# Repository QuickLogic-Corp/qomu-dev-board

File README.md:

# qomu-dev-board
Qomu Development Board for EOS S3

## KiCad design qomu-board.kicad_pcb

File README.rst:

======================
Qomu Development Board
======================

.. figure:: img/qomu-board.png

Overview
========

This repository contains open hardware design files for a development board based on the Quicklogic `EOS S3 Sensor Processing Platform <https://www.quicklogic.com/products/eos-s3/>`_.
The design files were created by `Antmicro <https://www.antmicro.com>`_ in cooperation with `Quicklogic <https://www.quicklogic.com/>`_.
The board is small enough to fit into a USB socket.
This allows the user to explore functionalities of the EOS S3 platform on the go without cables or taking up space on your desk.
The board has an additional break-away part with debug connectors that speed up initial bringup and software development.

Key features
============

* EOS S3 Sensor Processing Platform
* 16Mbit of external flash memory
* Accelerometer
* User RGB LED
* Capacitive touch pads
* Supplied with 5.0VDC from USB port
* USB data signals tied to programmable logic

Layout and dimensions
=====================

.. figure:: img/qomu-layout.png

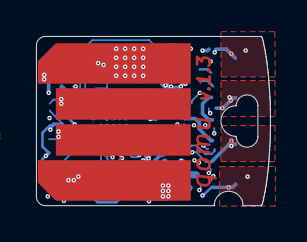
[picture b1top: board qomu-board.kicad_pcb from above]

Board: 4 copper layers, 13.0 x 9.4 mm, 52 parts (0 on the bottom side), 36 nets.

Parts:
C1, C2, C7, C9: 2u2, 10V, X5R, 0201; C_0201_0603Metric
C3, C5, C6, C8, C10, C11: 100n, 6.3V, X5R, 0201; C_0201_0603Metric
C4: 1u, 6.3V, X5R, 0201; C_0201
C13, C14: 8p, 25V, NP0, 0201; C_0201_0603Metric
C15: 1u, 6.3V, X5R, 0201; C_0201_0603Metric
D1, D2, D3, D4, D6, D7: D5V0L1B2LP3-7; X1-DFN1006-2
D5: VCUT05E1-SD0; X1-DFN1006-2
IC1: EOS-S3; 42-WLCSP
N1: oshw_logo; OSHW-Logo2_7.3x6mm_Copper_Mask
N2: antmicro_logo; antmicro-logo_midlayer_4mm
N3: ql_logo; Ql_logo_mid_9mm
Q1, Q2, Q3: RV1C002UN; VML0806
R1, R2, R5: 10k, 1%, 0201; R_0201_0603Metric
R9: 1k5, 1%, 0201; R_0201_0603Metric
R11, R12: 22R, 1%, 0201; R_0201_0603Metric
R16, R17: 100R, 1%, 0201; R_0201_0603Metric
R18: 220R, 1%, 0201; R_0201_0603Metric
SW2: Captouch Pads; captouch-edge
TP2, TP3, TP8: TP_SMD_0_75MM; Testpoint_smd_0_75_0_6mm
TP4, TP5, TP6, TP7: TP_SMD_0_75MM; Testpoint_pad_1mm
U1, U2: MIC5504-3.3YMT; Texas_X2SON-4_1x1mm_P0.65mm
U3: NCP803; SC-70_SOT-323
U4: GD25Q16CEIGR
U9: USB-B; USB-PCB
U10: UHD1110-FKA; LED-RGB-5DS-UHD1110-FKA
XTAL1: ECS-_327-12_5-1210-TR; XTAL_ECS-.327-12.5-1210-TR

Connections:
+3V3: C3.1, C5.2, C6.1, C8.1, C9.1, IC1.B3, IC1.C2, IC1.C6, R1.2, U2.1, U4.3, U4.7, U4.8, U10.4
+VBUS: C1.1, C2.1, D5.1, U1.3, U1.4, U2.3, U2.4, U9.1
/C1: IC1.C1, TP3.1
/LED_B: IC1.F4, Q3.1
/LED_BK: R16.2, U10.1
/LED_G: IC1.A6, Q2.1
/LED_GK: R17.2, U10.2
/LED_R: IC1.D2, Q1.1
/LED_RK: R18.2, U10.3
/PU_CTRL_USBP: IC1.E2, R9.1
/RST_N: IC1.F1, R1.1, U3.2
/R_USB_N: IC1.F3, R11.1
/R_USB_P: IC1.E4, R12.1
/SPI_MISO: IC1.F5, TP7.1, U4.2
/SPI_MOSI: IC1.E6, TP4.1, U4.5
/SPI_SCLK: IC1.D5, TP6.1, U4.6
/SPI_SS: IC1.F6, TP5.1, U4.1
/SWD_CLK: IC1.A4, TP8.1
/SWD_IO: IC1.B4, TP2.1
/TOUCH_1: D4.1, IC1.B5, SW2.1
/TOUCH_2: D2.1, IC1.D1, SW2.2
/TOUCH_3: D3.1, IC1.A7, SW2.3
/TOUCH_4: D1.1, IC1.E3, SW2.4
/USB_N: D7.1, R11.2, U9.2
/USB_P: D6.1, R9.2, R12.2, U9.3
/VCCIOB: C7.1, C10.1, C11.1, IC1.D6, IC1.D7, U1.1, U3.3
/VDD1: C4.1, IC1.A2
/VDD2: C15.1, IC1.A3
GND: C1.2, C2.2, C3.2, C4.2, C5.1, C6.2, C7.2, C8.2, C9.2, C10.2, C11.2, C13.2, C14.2, C15.2, D1.2, D2.2, D3.2, D4.2, D5.2, D6.2, D7.2, IC1.C3, IC1.C4, IC1.C5, IC1.D4, IC1.E5, Q1.2, Q2.2, Q3.2, R2.2, R5.1, U1.2, U1.5, U2.2, U2.5, U3.1, U4.4, U9.4
unnamed: C13.1, IC1.B1, XTAL1.1
unnamed: C14.1, IC1.A1, XTAL1.2
unnamed: IC1.A5, R2.1
unnamed: IC1.B6, R5.2
unnamed: Q1.3, R18.1
unnamed: Q2.3, R17.1
unnamed: Q3.3, R16.1

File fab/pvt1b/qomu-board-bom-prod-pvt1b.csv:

Reference,Value,Footprint,Count,Datasheet,FootprintLib,MPN,Manufacturer,SZLCSC_1k_RMB,SZLCSC_URL,DEBUG,Description
U10,UHD1110-FKA,LED-RGB-5DS-UHD1110-FKA,1,https://www.cree.com/led-components/media/documents/ds-UHD11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,qomu-board-footprints,UHD1110-FKA,Cree,,,,
R12,"22R, 1%, 0201",R_0201_0603Metric,1,,qomu-board-footprints,MCRE000100,Multicomp,,,,
R9,"1k5, 1%, 0201",R_0201_0603Metric,1,,qomu-board-footprints,MCRE000144,Multicomp,,,,
D1,D5V0L1B2LP3-7,X1-DFN1006-2,1,https://www.diodes.com/assets/Datasheets/D5V0L1B2LP3.pdf,qomu-board-footprints,D5V0L1B2LP3-7,Diodes Inc.,,,,
D2,D5V0L1B2LP3-7,X1-DFN1006-2,1,https://www.diodes.com/assets/Datasheets/D5V0L1B2LP3.pdf,qomu-board-footprints,D5V0L1B2LP3-7,Diodes Inc.,,,,
D3,D5V0L1B2LP3-7,X1-DFN1006-2,1,https://www.diodes.com/assets/Datasheets/D5V0L1B2LP3.pdf,qomu-board-footprints,D5V0L1B2LP3-7,Diodes Inc.,,,,
D4,D5V0L1B2LP3-7,X1-DFN1006-2,1,https://www.diodes.com/assets/Datasheets/D5V0L1B2LP3.pdf,qomu-board-footprints,D5V0L1B2LP3-7,Diodes Inc.,,,,
D6,D5V0L1B2LP3-7,X1-DFN1006-2,1,https://www.diodes.com/assets/Datasheets/D5V0L1B2LP3.pdf,qomu-board-footprints,D5V0L1B2LP3-7,Diodes Inc.,,,,
D7,D5V0L1B2LP3-7,X1-DFN1006-2,1,https://www.diodes.com/assets/Datasheets/D5V0L1B2LP3.pdf,qomu-board-footprints,D5V0L1B2LP3-7,Diodes Inc.,,,,
D5,VCUT05E1-SD0,X1-DFN1006-2,1,http://www.vishay.com/docs/85900/vcut05e1-sd0.pdf,qomu-board-footprints,D5V0L1B2LP3-7,Diodes Inc.,,,,
R1,"10k, 1%, 0201",R_0201_0603Metric,1,,qomu-board-footprints,ERJ1GNF1002C ,Panasonic,,,,
R11,"22R, 1%, 0201",R_0201_0603Metric,1,,qomu-board-footprints,MCRE000100 ,Multicomp,,,,
C2,"2u2, 10V, X5R, 0201",C_0201_0603Metric,1,,qomu-board-footprints,CL03A225MP3CRNC ,Samsung,,,,
C9,"2u2, 10V, X5R, 0201",C_0201_0603Metric,1,,qomu-board-footprints,CL03A225MP3CRNC ,Samsung,,,,
U4,GD25Q16CEIGR,GD25Q16CEIGR,1,http://www.gigadevice.com/datasheet/gd25q16c/,qomu-board-footprints,GD25Q16CEIGR,GigaDevice Semiconductor,,,,
C5,"100n, 6.3V, X5R, 0201",C_0201_0603Metric,1,,qomu-board-footprints,GRM033R60J104KE19D ,Murata,,,,
U2,MIC5504-3.3YMT,Texas_X2SON-4_1x1mm_P0.65mm,1,,qomu-board-footprints,MIC5504-3.3YMT,Microchip,0.5733,https://item.szlcsc.com/86372.html,,
C3,"100n, 6.3V, X5R, 0201",C_0201_0603Metric,1,,qomu-board-footprints,GRM033R60J104KE19D,Murata,,,,
C6,"100n, 6.3V, X5R, 0201",C_0201_0603Metric,1,,qomu-board-footprints,GRM033R60J104KE19D,Murata,,,,
C8,"100n, 6.3V, X5R, 0201",C_0201_0603Metric,1,,qomu-board-footprints,GRM033R60J104KE19D,Murata,,,,
C10,"100n, 6.3V, X5R, 0201",C_0201_0603Metric,1,,qomu-board-footprints,GRM033R60J104KE19D,Murata,,,,
C11,"100n, 6.3V, X5R, 0201",C_0201_0603Metric,1,,qomu-board-footprints,GRM033R60J104KE19D,Murata,,,,
U1,MIC5504-3.3YMT,Texas_X2SON-4_1x1mm_P0.65mm,1,,qomu-board-footprints,MIC5504-3.3YMT,Microchip,0.5733,https://item.szlcsc.com/86372.html,,
C7,"2u2, 10V, X5R, 0201",C_0201_0603Metric,1,,qomu-board-footprints,CL03A225MP3CRNC ,Samsung,,,,
C1,"2u2, 10V, X5R, 0201",C_0201_0603Metric,1,,qomu-board-footprints,CL03A225MP3CRNC ,Samsung,,,,
R5,"10k, 1%, 0201",R_0201_0603Metric,1,,qomu-board-footprints,ERJ1GNF1002C ,Panasonic,,,,
R2,"10k, 1%, 0201",R_0201_0603Metric,1,,qomu-board-footprints,ERJ1GNF1002C ,Panasonic,,,,
R16,"100R, 1%, 0201",R_0201_0603Metric,1,,qomu-board-footprints,MCRE000116 ,Multicomp,,,,
R17,"100R, 1%, 0201",R_0201_0603Metric,1,,qomu-board-footprints,MCRE000116 ,Multicomp,,,,
R18,"220R, 1%, 0201",R_0201_0603Metric,1,,qomu-board-footprints,MCRE000124,Multicomp,,,,
Q2,RV1C002UN,VML0806,1,https://d1d2qsbl8m0m72.cloudfront.net/en/products/databook/d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,qomu-board-footprints,RV1C002UN,ROHM Semiconductor,,,,Nch 20V 180mA Small Signal MOSFET
Q3,RV1C002UN,VML0806,1,https://d1d2qsbl8m0m72.cloudfront.net/en/products/databook/d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,qomu-board-footprints,RV1C002UN,ROHM Semiconductor,,,,Nch 20V 180mA Small Signal MOSFET
Q1,RV1C002UN,VML0806,1,https://d1d2qsbl8m0m72.cloudfront.net/en/products/databook/d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,qomu-board-footprints,RV1C002UN,ROHM Semiconductor,,,,Nch 20V 180mA Small Signal MOSFET
C14,"8p, 25V, NP0, 0201",C_0201_0603Metric,1,,qomu-board-footprints,GRM0335C1E8R0DA01D,Murata,,,,
C13,"8p, 25V, NP0, 0201",C_0201_0603Metric,1,,qomu-board-footprints,GRM0335C1E8R0DA01D,Murata,,,,
XTAL1,ECS-_327-12_5-1210-TR,XTAL_ECS-.327-12.5-1210-TR,1,https://ecsxtal.com/store/pdf/ECX-1210.pdf,qomu-board-footprints,ECS-.327-12.5-1210-TR,ECS Inc.,6.28,https://item.szlcsc.com/432480.html,,
IC1,EOS-S3,42-WLCSP,1,https://www.quicklogic.com/wp-content/uploads/2019/05/QL_EOS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,qomu-board,EOS-S3-42-WLCSP,Quicklogic,,,,
C4,"1u, 6.3V, X5R, 0201",C_0201_0603Metric,1,,qomu-board-footprints,GRM033R60J105MEA2D,Murata,,,,
C15,"1u, 6.3V, X5R, 0201",C_0201_0603Metric,1,,qomu-board-footprints,GRM033R60J105MEA2D,Murata,,,,
U3,NCP803,SC-70_SOT-323,1,,qomu-board-footprints,MAX803SQ120T1G,On Semiconductor,,,,

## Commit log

2019-12-27 Initial files for qomu board
2019-12-27 Initial upload of lib folder for Qomu board
2019-12-27 Continue with initial upload of Qomu files
2019-12-27 More files for Qomu initial upload
2020-04-17 Add PDF of the qomu board schematic
2020-04-17 Update Kicad design file
2020-04-18 Update Qomu design with latest design files and generated gerber
2020-08-07 Schematic Update: 1. Remove accel sensor and related passive components 2. Add QL to title Layout Update: 1. Remove accel sensor and related passive components 2. Remove stranded nets: I2C SCL, I2C S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
    Remains: check stranded via for 3.3V and GND
2020-09-02 lib: add usb-c connector
    Add a USB-C socket.
2020-09-02 lib: add USB-C schematic information to library
2020-09-02 fp-info-cache: check in updated cache file
    KiCad updates this file for some reason. Check in the new version of
    this cache.
2020-09-02 gitattributes: add attributes file
    When switching between Windows and Unix systems, line endings can
    change. KiCad on Windows adds <LF>, whereas other platforms don't add
    this.
    By checking in this .gitattributes file, these differences can be
    ignored.
2020-09-02 sch: add USB-C connector and clarify part numbers
    Add a USB-C connector to the schematic to enable testing without having
    Qomu sit physically inside of a USB port.
2020-09-02 sch: note that debug area is breakaway
    Add a note that the programming/debug area is designed to be torn off
    after production.
2020-09-02 pdf: update board schematic
    This adds a USB port to the breakaway/debug area.
2020-09-02 lib: add footprints for USB-C port
    Add a 3D model and footprint for a USB-C port.
2020-09-02 reference: add reference manual for USB-C port
    Add the mechanical drawing and datasheet for the USB-C port.
2020-09-02 sch: update C12 with full value
2020-09-02 sch: unify part descriptions
    Some parts had incorrect and/or nonstandard descriptions. Unify these.
2020-09-02 lib: add datasheet url for mosfet
2020-09-02 lib: unify field names for usb-c connector
2020-09-07 sch: add "DNP" for TP7
    This pad was missed, and was caught by the PCB assembly house.
2020-09-10 lib: increase schematic lead length for USB-C
    The previous leads for the USB-C connector caused the pinout names to
    spill into the part itself.
2020-09-10 doc: move reference docs from lib/ to doc/
2020-09-10 qomu-board: utilise new USB-C schematic symbol
2020-09-10 pcb: first attempt at new component placement
    There's still a huge ratsnest, but component placement should roughly be
    finalized.
2020-09-11 pcb: re-layout board with new design rules
    This lays out the board according to the design rules set forth by the
    factory.
2020-09-11 pcb: fix routing and drc errors
    This fixes all unconnected nets and DRC warnings/errors, and is ready
    for fabrication.
2020-09-11 lib: usb-c: set pins 2-4 to SHELL
    These were previously unconnected. Add phantom pins for these values and
    stack them on top of each other so they are all connected to the same
    net.
2020-09-11 sch: adjust some pinouts to make routing easier
    These pinout values make routing from the inner row much easier.
2020-09-11 lib: add castellated via and 1mm testpoints
    1mm testpoints are much easier to build jigs for.
    Castellated vias are used to break off the test jig.
2020-09-11 gitattributes: ignore line endings on libraries and projects
2020-09-11 cache: add information on new libraries
2020-09-11 project: adjust defaults for via diameter
    Set the diameter based on the design rules given to us by the factory.
2020-09-11 sch: annotate which components are for DEBUG
    These components can be left out of production builds.
2020-09-11 pcb: fix touchpads on backside
    The touchpads didn't extend to the backside.
2020-09-12 pcb: redo layout in 4-layers
    Remove two of the layers, since they were mostly empty anyway.
2020-09-12 gitattributes: add kicad_pcb to text,lf entry
    This keeps git from rewriting the whole file every time.
2020-09-12 pcb: move logos from copper to comment layer
    There are two logos that were on a copper layer. Since this layer has
    been removed, move the logos to the user comments layer.
2020-09-12 pcb: fix phantom In.Cu4 vias
    There were two vias that were still going to In.Cu4 despite this layer
    no longer existing.
2020-09-12 pcb: re-enable all copper layer visibility
2020-09-12 pro: set layer count to 4
2020-09-12 gitattributes: mark cache file as text
2020-09-12 fp-info-cache: commit updated cache file
    It is unclear what has changed.
2020-09-16 sch: add test points for SWDIO/SWCLK
    These will be necessary if we are to make a test jig that can do
    interactive debugging.
2020-09-16 pcb: lay out new SWD pads
2020-09-16 pcb: tag dvt1c
2020-09-16 pcb: fix silkscreen layers
    Some components were showing on the silkscreen layer, which wasn't what
    we wanted. This caused overlapping of pads.
    Disable the reference designator on those pards.
2020-09-16 cache: update cache serial number
2020-09-16 pcb: move VUSB trace to "front" side
    By moving this trace to the font side, we allow the ground plane on the
    back side to continue uninterrupted.
2020-09-16 pdf: regenerate schematic
2020-09-16 doc: add datasheet for main processor
2020-09-16 pcb: fix pin1 silkscreen for led transistors
    The pin1 marker was extending onto the testpoint, which would cause
    manufacturing issues.
2020-09-16 pcb: gnd: increase via spacing due to DRC check
    The PCB house said the GND vias were too close. Move them further apart
    to prevent design issues.
2020-09-16 pcb: fix kicad soldermask values
    These values are completely wrong for small PCBs such as Qomu. By
    default, it leaves a massive gap between the soldermask and the part,
    resulting in no soldermask on the part itself.
    Fix the "default" value of 0.25 by setting it to 0.05, which is what
    Fomu used.
2020-09-18 sch: fix part number for 5.1k resistor
    It was still listed as a part for a 10k resistor.
2020-09-18 pcb: fix soldermask pullback -- again
    Kicad defaults to large soldermask pullbacks, which works fine with
    large parts but creates many many solderability issues with fine-pitch
    parts such as those used on Qomu. Fix this so we get an actual
    soldermask on our parts.
2020-10-29 pcb: fill in Fab layer
    This fills in the fabrication layer, which is required to do
    pick-and-place. Ordinarily, designators are used to set up the
    pick-and-place machine, however we don't have any silk on this PCB. As a
    result, this separate fab layer is required.
2020-11-03 pcb: fix Fab layer for components
    This is required to get assembly at the factory.
2020-11-19 sch: add VDD1 and VDD2 decoupling caps
    These were missing in the original design, and end up being very
    important.
2020-11-19 lib: fix pin 1 outline for SWD connector
    This was previously underspecified.
2020-11-19 fp-info-cache: commit new cache hash
    No significant changes.
2020-11-19 pcb: add bulk caps for VDD1 and VDD2
    This adds these two capacitors and keeps everything else.
2020-12-02 lib: add SOT-323 for Reset Circuit
    This device has a SOT-323 footprint that's different from the one in
    KiCad. Add the footprint from the reference manual.
2020-12-02 sch: add reset circuit to PCB
    This is required to keep the CPU in reset when the voltage has just been
    applied.
2020-12-02 pcb: add reset circuit to PCB
2020-12-02 pcb: re-fill pours
2020-12-02 doc: add reset generator documentation
2020-12-05 lib: use correct part number for reset circuit
    The previous part number was an incorrect footprint. Specify the correct
    part number.
2020-12-05 fp-info-cache: sync this file
2020-12-05 sch: use correct reset circuit
    Previously, we were specifying an incorrect part number.
2020-12-05 pcb: re-import schematic (no changes)
    This simply re-imports the schematic, which results in no new changes.
2020-12-05 pro: update output path with pvt2b
    This simply updates the file path to specify fab/pvt2b.
2020-12-05 fab: add pvt1b
    This is a release candidate.
2020-12-16 pcb: specify soldermask as red
2021-01-14 fp-info-cache: update this file
    No idea what changed.
2021-01-14 lib: fix footprint paths
    Many footprints were unusable when imported into FreeCAD. This fixes
    everything so that an import actually works.
2021-01-14 gitattributes: add step and stp
2021-01-14 qomu: remove debug area
    This is unused on production devices.
2021-01-14 case: add initial case design
2021-03-24 Update to latest HW revision

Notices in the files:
qomu-board.kicad_pcb:
License: CC-BY-SA 4.0 or TAPR
